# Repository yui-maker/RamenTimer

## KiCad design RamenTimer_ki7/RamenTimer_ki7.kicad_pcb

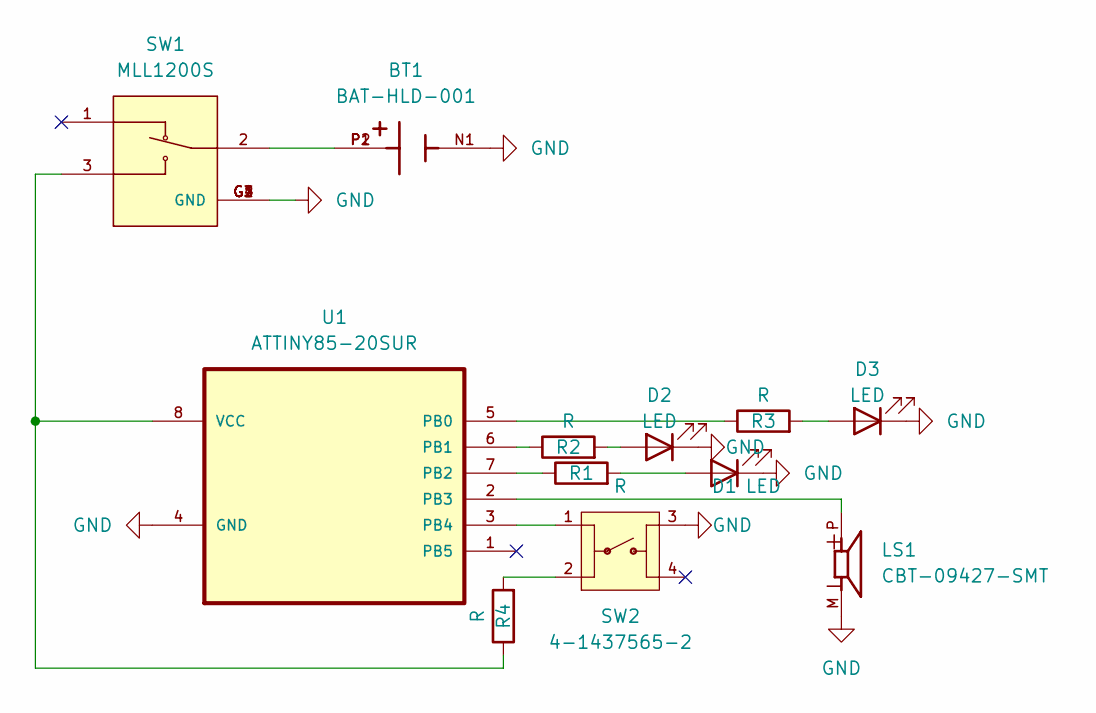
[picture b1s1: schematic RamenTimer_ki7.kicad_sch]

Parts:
BT1: BAT-HLD-001; BAT_BAT-HLD-001; PARTREV C
D1, D2, D3: LED; LED_0805_2012Metric_Pad1.15x1.40mm_HandSolder
LS1: CBT-09427-SMT; CUI_CBT-09427-SMT
R1, R2, R3, R4: R; R_0805_2012Metric_Pad1.20x1.40mm_HandSolder
SW1: MLL1200S; SW_MLL1200S; PARTREV A2
SW2: 4-1437565-2; SW_4-1437565-2; PARTREV V
U1: ATTINY85-20SUR; SOIC127P798X216-8N; MPN ATTINY85-20SUR

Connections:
GND: BT1.N1, D1.1 (K), D2.1 (K), D3.1 (K), LS1.M, SW1.G1 (GND), SW1.G2 (GND), SW1.G3 (GND), SW1.G4 (GND), SW2.3, U1.4 (GND)
unnamed: BT1.P1, BT1.P2, SW1.2
unnamed: D1.2 (A), R1.2
unnamed: D2.2 (A), R2.2
unnamed: D3.2 (A), R3.2
unnamed: R4.2, SW2.2
unnamed: R3.1, U1.5 (PB0)
unnamed: R2.1, U1.6 (PB1)
unnamed: R1.1, U1.7 (PB2)
unnamed: LS1.P, U1.2 (PB3)
unnamed: SW2.1, U1.3 (PB4)
unnamed: R4.1, SW1.3, U1.8 (VCC)

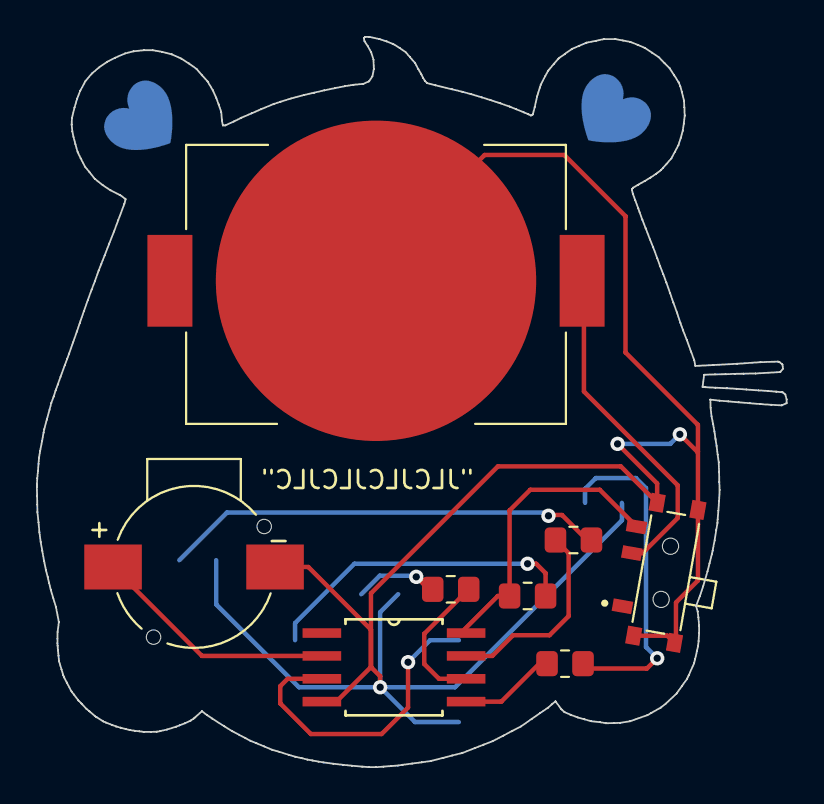
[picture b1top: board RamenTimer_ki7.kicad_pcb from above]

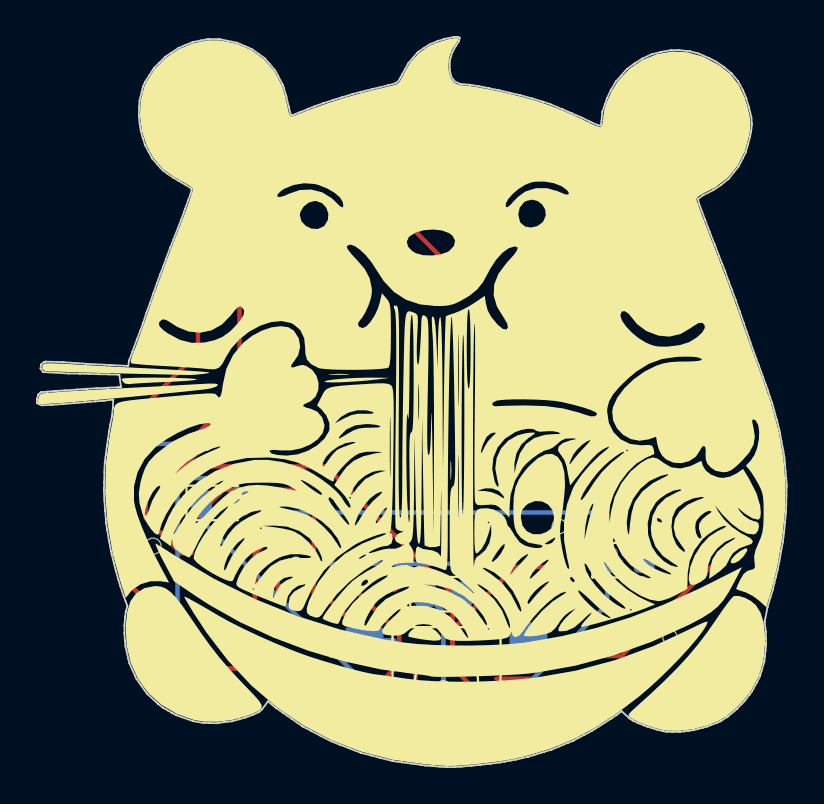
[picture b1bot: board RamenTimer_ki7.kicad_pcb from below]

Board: 2 copper layers, 41.7 x 40.6 mm, 12 parts (4 on the bottom side), 12 nets.

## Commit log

2024-01-29 timer code and PCB
